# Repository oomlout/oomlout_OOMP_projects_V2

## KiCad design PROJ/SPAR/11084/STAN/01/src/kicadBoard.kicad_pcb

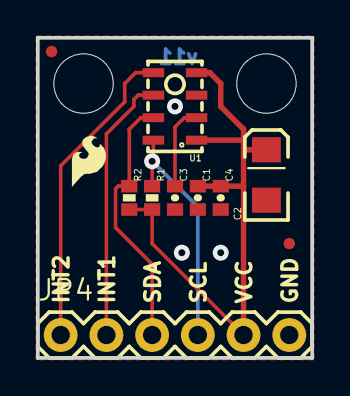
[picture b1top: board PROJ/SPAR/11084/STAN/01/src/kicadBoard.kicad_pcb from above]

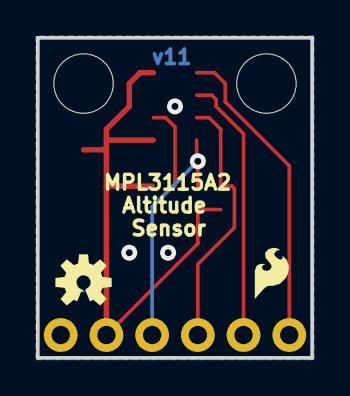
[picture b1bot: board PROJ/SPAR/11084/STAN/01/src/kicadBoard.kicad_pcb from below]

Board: 2 copper layers, 15.2 x 17.8 mm, 16 parts (2 on the bottom side), 7 nets.

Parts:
C1, C3: 0.1uF; 0402-CAP
C2: 10uF; EIA3216
C4: 1uF; 0402-CAP
JP1, JP5: LOGO-SFESK; SFE-LOGO-FLAME
JP2, JP3: STAND-OFF
JP4: 1X06
JP6, JP7: FIDUCIALUFIDUCIAL; MICRO-FIDUCIAL
R1, R2: 1k; 0402-RES
U1: MPL3115A2LGA8; LGA8
U$1: OSHW-LOGOS; OSHW-LOGO-S
U$2: CREATIVE_COMMONS

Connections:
GND: C1.2, C2.C, C3.2, C4.2, JP4.6, U1.3
INT1: JP4.2, U1.6
INT2: JP4.1, U1.5
unnamed: C3.1, U1.2
SCL: JP4.4, R1.1, U1.8
SDA: JP4.3, R2.1, U1.7
VCC: C1.1, C2.A, C4.1, JP4.5, R1.2, R2.2, U1.1, U1.4

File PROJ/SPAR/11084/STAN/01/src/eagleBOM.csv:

"Part";"Value";"Device";"Package";"Description";"";
"C1";"0.1uF";"CAP0402-CAP";"0402-CAP";"Capacitor";"";
"C2";"10uF";"CAP_POL1206";"EIA3216";"Capacitor Polarized";"";
"C3";"0.1uF";"CAP0402-CAP";"0402-CAP";"Capacitor";"";
"C4";"1uF";"CAP0402-CAP";"0402-CAP";"Capacitor";"";
"JP1";"LOGO-SFESK";"LOGO-SFESK";"SFE-LOGO-FLAME";"Spark Fun Electronics PCB Logo";"";
"JP2";"STAND-OFF";"STAND-OFF";"STAND-OFF";"Stand Off";"";
"JP3";"STAND-OFF";"STAND-OFF";"STAND-OFF";"Stand Off";"";
"JP4";"";"M06SIP";"1X06";"Header 6";"";
"JP5";"LOGO-SFESK";"LOGO-SFESK";"SFE-LOGO-FLAME";"Spark Fun Electronics PCB Logo";"";
"JP6";"FIDUCIALUFIDUCIAL";"FIDUCIALUFIDUCIAL";"MICRO-FIDUCIAL";"Fiducial Alignment Points";"";
"JP7";"FIDUCIALUFIDUCIAL";"FIDUCIALUFIDUCIAL";"MICRO-FIDUCIAL";"Fiducial Alignment Points";"";
"R1";"1k";"RESISTOR0402-RES";"0402-RES";"Resistor";"";
"R2";"1k";"RESISTOR0402-RES";"0402-RES";"Resistor";"";
"U$1";"OSHW-LOGOS";"OSHW-LOGOS";"OSHW-LOGO-S";"Open Source Hardware Logo This logo indicates the piece of hardware it is found on incorporates a OSHW license and/or adheres to the definition of open source hardware found here: http://freedomdefined.org/OSHW";"";
"U$2";"CREATIVE_COMMONS";"CREATIVE_COMMONS";"CREATIVE_COMMONS";"";"";
"U1";"MPL3115A2LGA8";"MPL3115A2LGA8";"LGA8";"Altimeter/Pressure Sensor, I2C, 1.95V-3.6V supply, 50 to 110kPa";"";

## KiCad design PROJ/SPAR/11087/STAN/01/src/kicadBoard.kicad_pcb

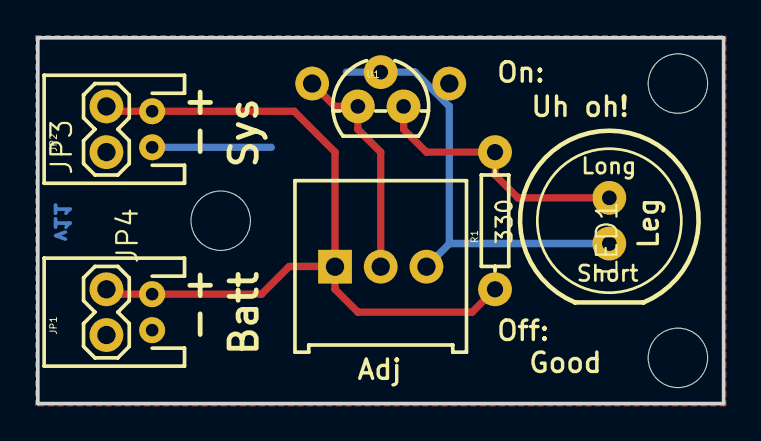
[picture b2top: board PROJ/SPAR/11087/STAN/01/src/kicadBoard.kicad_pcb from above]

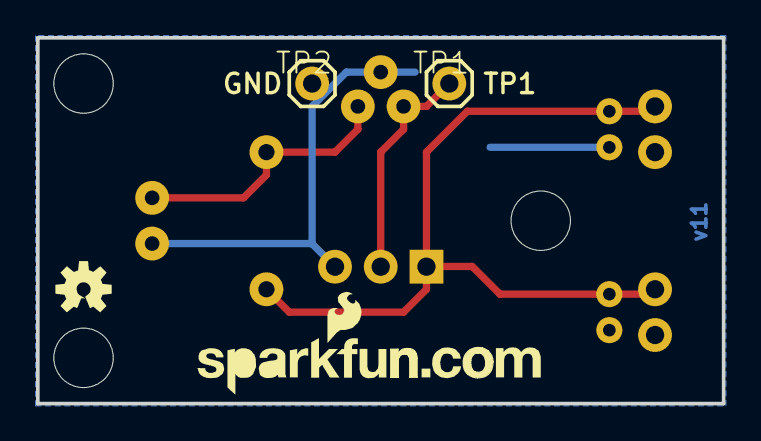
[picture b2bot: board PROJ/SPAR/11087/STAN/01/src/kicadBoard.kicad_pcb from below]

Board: 2 copper layers, 38.1 x 20.3 mm, 16 parts (4 on the bottom side), 4 nets.

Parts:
JP1: Battery; JST-2-PTH
JP2: System; JST-2-PTH
JP3, JP4: 1X02
JP31, JP41, JP61: STAND-OFF
JP51: LOGO-SFENEW; SFE-NEW-WEBLOGO
LED1: Green; LED10MM-2
R1: 330; AXIAL-0.3
RADJ0: 10K; 3386U
TP1: TP1; 1X01
TP2: TP2; 1X01
U1: TL431; TO-92
U$1: OSHW-LOGOS; OSHW-LOGO-S
U$2: CREATIVE_COMMONS

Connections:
GND: JP1.1, JP2.1, JP3.1, JP4.2, LED1.K, RADJ0.3, TP2.1, U1.2
VCC: JP1.2, JP2.2, JP3.2, JP4.1, R1.P$1, RADJ0.1
VCUTOFF: RADJ0.2, TP1.1, U1.1
VOUT: LED1.A, R1.P$2, U1.3

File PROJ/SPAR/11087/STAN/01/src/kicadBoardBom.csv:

"Id";"Designator";"Package";"Quantity";"Designation";"Supplier and ref";
1;"U$2";"CREATIVE_COMMONS";1;"CREATIVE_COMMONS";;;
2;"JP31,JP41,JP61";"STAND-OFF";3;"STAND-OFF";;;
3;"U1";"TO-92";1;"TL431";;;
4;"RADJ0";"3386U";1;"10K";;;
5;"JP1";"JST-2-PTH";1;"Battery";;;
6;"JP3,JP4";"1X02";2;"";;;
7;"LED1";"LED10MM-2";1;"Green";;;
8;"JP2";"JST-2-PTH";1;"System";;;
9;"R1";"AXIAL-0.3";1;"330";;;
10;"TP1";"1X01";1;"TP1";;;
11;"JP51";"SFE-NEW-WEBLOGO";1;"LOGO-SFENEW";;;
12;"U$1";"OSHW-LOGO-S";1;"OSHW-LOGOS";;;
13;"TP2";"1X01";1;"TP2";;;

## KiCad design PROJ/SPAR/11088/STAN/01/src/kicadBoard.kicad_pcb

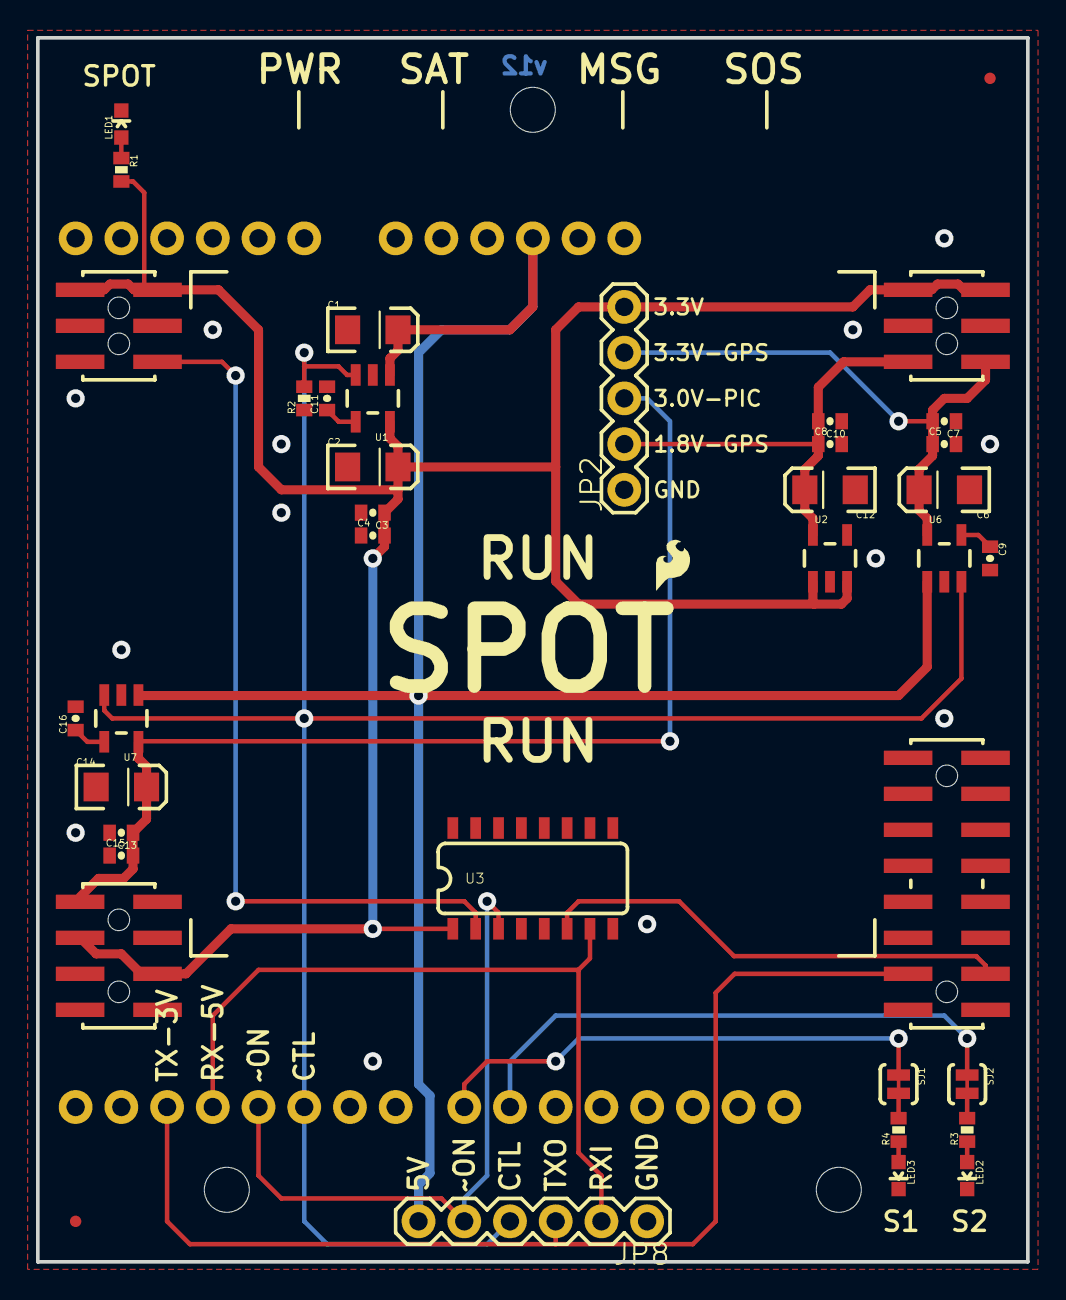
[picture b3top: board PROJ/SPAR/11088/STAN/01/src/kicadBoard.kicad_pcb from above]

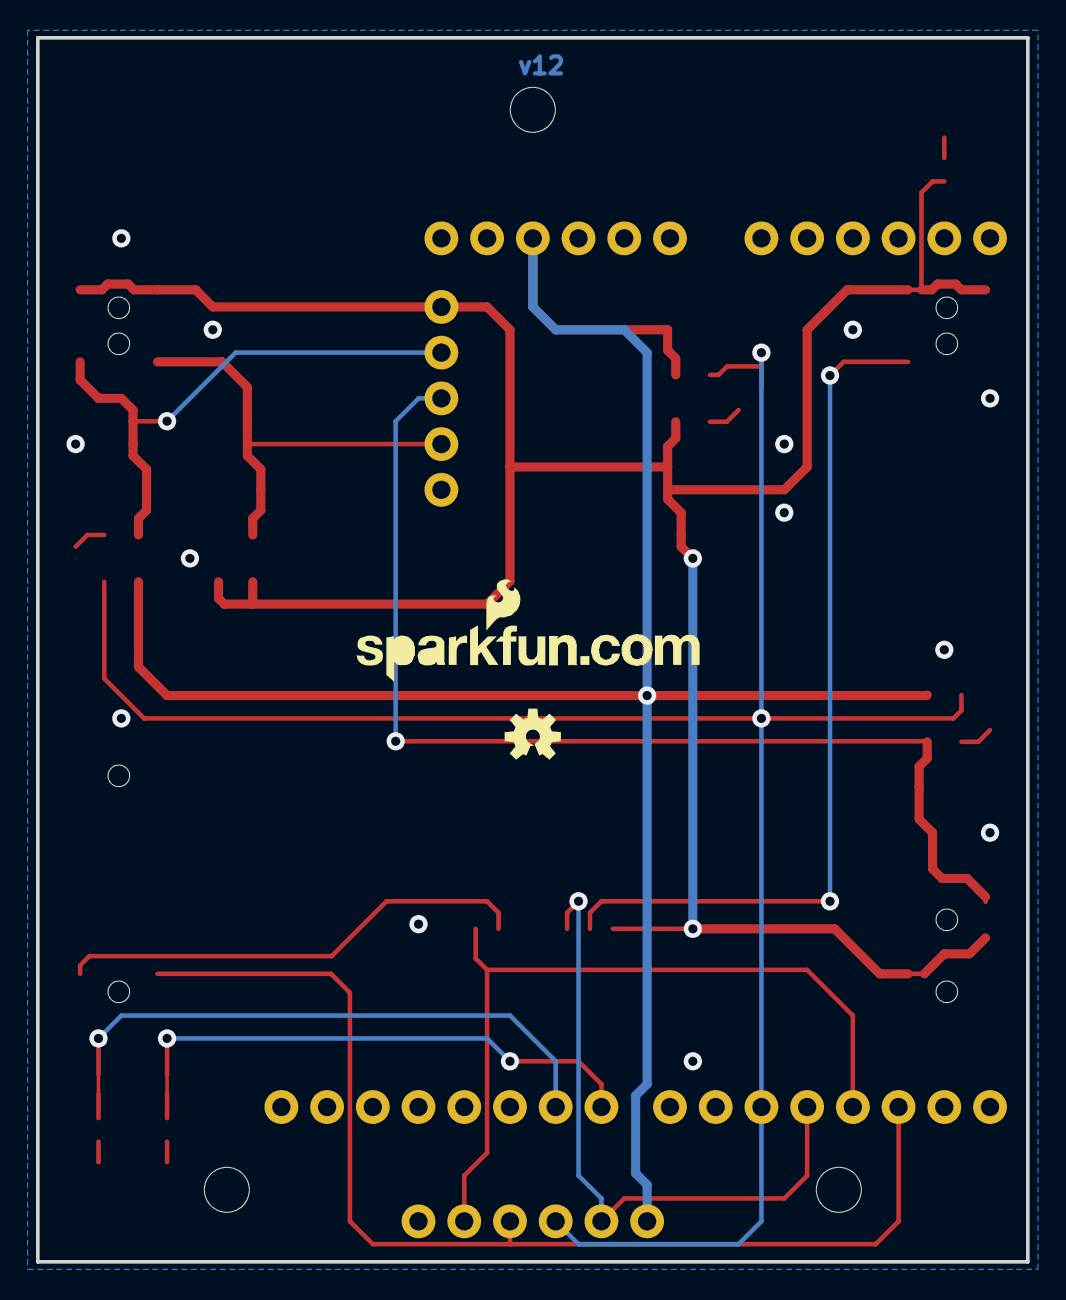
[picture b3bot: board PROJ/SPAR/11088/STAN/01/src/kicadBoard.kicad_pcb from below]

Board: 2 copper layers, 55.0 x 68.0 mm, 40 parts (2 on the bottom side), 22 nets.

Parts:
C1, C2, C6, C12, C14: 10uF; EIA3216
C3, C5, C8, C13: 1uF; 0402-CAP
C4, C7, C10, C15: 0.1uF; 0402-CAP
C9, C11, C16: 470nF; 0402-CAP
JP2: 1X05
JP8: 1X06
JP10, JP11: FIDUCIALUFIDUCIAL; MICRO-FIDUCIAL
LED1: Red; LED-0603
LED2: Blue; LED-0603
LED3: Green; LED-0603
R1, R3, R4: 330; 0402-RES
R2: 10K; 0402-RES
SJ1, SJ2: SJ_2S-TRACE
U1: MIC5219-3.3; SOT23-5
U2: AP7311-1.8; SOT23-5
U3: 74HC4050; SO016
U4: SPOT-CONNECT
U5: ARDUINO_SHIELD; DUEMILANOVE_VIAS
U6, U7: MIC5219-3.0; SOT23-5
U$1: LOGO-SFESK; SFE-LOGO-FLAME
U$2: CREATIVE_COMMONS
U$3: OSHW-LOGOS; OSHW-LOGO-S
U$11: LOGO-SFENEW; SFE-NEW-WEBLOGO

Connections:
1.8V-GPS: C8.1, C10.2, C12.A, JP2.2, U2.5, U4.1.8V-GPS
3.3V: C2.A, C3.1, C4.2, JP2.5, R1.2, U1.5, U2.1, U2.3, U3.1, U4.3.3V@1, U4.3.3V@2, U4.3.3V@3, U4.3.3V@4, U4.3VMSP, U4.BATT
3V-GPS: C5.1, C6.A, C7.2, JP2.4, U4.3V-GPS, U6.5
3V-PIC: C13.1, C14.A, C15.2, JP2.3, U4.3VPIC, U7.5
5V: C1.A, JP8.6, U1.1, U5.5V, U6.1, U7.1
GND: C1.C, C2.C, C3.2, C4.1, C5.2, C6.C, C7.1, C8.2, C9.2, C10.1, C11.2, C12.C, C13.2, C14.C, C15.1, C16.2, JP2.1, JP8.1, LED1.C, LED2.C, LED3.C, R2.1, U1.2, U2.2, U3.8, U4.GND@1, U4.GND@2, U4.GND@3, U4.GND@4, U4.GND@5, U5.GND@0, U5.GND@1, U5.GND@2, U6.2, U7.2
unnamed: C16.1, U7.4
unnamed: R4.2, SJ1.2
unnamed: R3.2, SJ2.2
unnamed: C9.1, U6.4
unnamed: LED2.A, R3.1
unnamed: LED3.A, R4.1
unnamed: SJ1.1, U5.D8
unnamed: SJ2.1, U5.D9
unnamed: C11.1, U1.4
unnamed: LED1.A, R1.1
PWRCTL: JP8.4, R2.2, U1.3, U5.D5, U6.3, U7.3
SPOT-RX-3V: U3.6, U4.BT-TX
SPOT-RX-5V: JP8.2, U3.7, U5.D3
SPOT-TX-3V: JP8.3, U4.BT-RX, U5.D2
~ON-3V: U3.2, U4.ON/OFF
~ON-5V: JP8.5, U3.3, U5.D4

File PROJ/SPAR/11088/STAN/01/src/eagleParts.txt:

Partlist

Exported from boardEagle.brd at 17/08/2022 19:31

EAGLE Version 9.6.2 Copyright (c) 1988-2020 Autodesk, Inc.

Assembly variant: 

Part     Value             Package          Library  Position (inch)       Orientation

C1       10uF              EIA3216          SparkFun (0.73 2.04)           R0
C2       10uF              EIA3216          SparkFun (0.73 1.74)           R0
C3       1uF               0402-CAP         SparkFun (0.73 1.64)           R180
C4       0.1uF             0402-CAP         SparkFun (0.73 1.59)           R0
C5       1uF               0402-CAP         SparkFun (1.98 1.79)           R0
C6       10uF              EIA3216          SparkFun (1.98 1.69)           R180
C7       0.1uF             0402-CAP         SparkFun (1.98 1.84)           R180
C8       1uF               0402-CAP         SparkFun (1.73 1.79)           R0
C9       470nF             0402-CAP         SparkFun (2.08 1.54)           R270
C10      0.1uF             0402-CAP         SparkFun (1.73 1.84)           R180
C11      470nF             0402-CAP         SparkFun (0.63 1.89)           R90
C12      10uF              EIA3216          SparkFun (1.73 1.69)           R180
C13      1uF               0402-CAP         SparkFun (0.18 0.94)           R180
C14      10uF              EIA3216          SparkFun (0.18 1.04)           R0
C15      0.1uF             0402-CAP         SparkFun (0.18 0.89)           R0
C16      470nF             0402-CAP         SparkFun (0.08 1.19)           R90
JP2                        1X05             SparkFun (1.28 1.69)           R90
JP8                        1X06             SparkFun (1.33 0.09)           R180
JP10     FIDUCIALUFIDUCIAL MICRO-FIDUCIAL   SparkFun (2.08 2.59)           R90
JP11     FIDUCIALUFIDUCIAL MICRO-FIDUCIAL   SparkFun (0.08 0.09)           R90
LED1     Red               LED-0603         SparkFun (0.18 2.49)           R0
LED2     Blue              LED-0603         SparkFun (2.03 0.19)           R180
LED3     Green             LED-0603         SparkFun (1.88 0.19)           R180
R1       330               0402-RES         SparkFun (0.18 2.39)           R270
R2       10K               0402-RES         SparkFun (0.58 1.89)           R90
R3       330               0402-RES         SparkFun (2.03 0.29)           R90
R4       330               0402-RES         SparkFun (1.88 0.29)           R90
SJ1                        SJ_2S-TRACE      SparkFun (1.88 0.39)           R270
SJ2                        SJ_2S-TRACE      SparkFun (2.03 0.39)           R270
U1       MIC5219-3.3       SOT23-5          SparkFun (0.73 1.89)           R180
U2       AP7311-1.8        SOT23-5          SparkFun (1.73 1.54)           R0
U3       74HC4050          SO016            SparkFun (1.08 0.84)           R0
U4       SPOT-CONNECT      SPOT-CONNECT     SparkFun (1.08 1.34)           R0
U5       ARDUINO_SHIELD    DUEMILANOVE_VIAS SparkFun (1.73 0.24)           R90
U6       MIC5219-3.0       SOT23-5          SparkFun (1.98 1.54)           R0
U7       MIC5219-3.0       SOT23-5          SparkFun (0.18 1.19)           R180

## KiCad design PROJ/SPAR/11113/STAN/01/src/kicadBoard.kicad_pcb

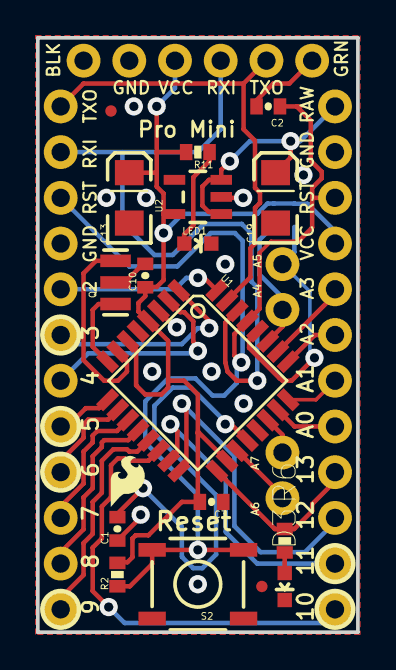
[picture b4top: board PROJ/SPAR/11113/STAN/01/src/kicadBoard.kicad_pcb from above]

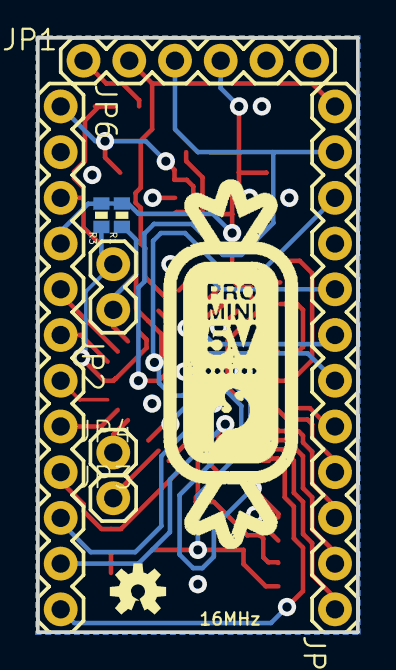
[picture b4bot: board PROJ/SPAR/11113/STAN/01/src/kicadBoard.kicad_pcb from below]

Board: 2 copper layers, 17.8 x 33.0 mm, 29 parts (10 on the bottom side), 32 nets.

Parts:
C1, C2, C3, C10: 0.1uF; 0402-CAP
C13, C19: 10uF; EIA3216
D3: Green; LED-0603
FRAME1: FRAME-LETTER; CREATIVE_COMMONS
JP1: FTDI Basic; 1X06
JP2: 1X02
JP3, JP4: 1X01
JP5, JP8: FIDUCIALUFIDUCIAL; MICRO-FIDUCIAL
JP6, JP7: 1X12
LED1: Red; LED-0603
Q1: 8/16/20MHz; RESONATOR-SMD
R1, R3: 0402-RES
R2, R11: 10K; 0402-RES
R6: 330; 0402-RES
S2: Reset; TACTILE_SWITCH_SMD
U1: ATMEGA328; TQFP32-08
U2: MIC5205; SOT23-5
U$1: LOGO-SFESK; SFE-LOGO-FLAME
U$2: PRO_MINI_CANDY
U$3: OSHW-LOGOS; OSHW-LOGO-S

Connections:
A0: JP6.8, U1.23
A1: JP6.7, U1.24
A2: JP6.6, U1.25
A3: JP6.5, U1.26
A4: JP2.1, R1.1, U1.27
A5: JP2.2, R3.1, U1.28
A6: JP3.1, U1.19
A7: JP4.1, U1.22
AREF: C1.2, U1.20
D2: JP7.8, U1.32
D3: JP7.7, U1.1
D4: JP7.6, U1.2
D5: JP7.5, U1.9
D6: JP7.4, U1.10
D7: JP7.3, U1.11
D8: JP7.2, U1.12
D9: JP7.1, U1.13
D10: JP6.12, U1.14
DTR: C2.2, JP1.1
GND: C1.1, C3.1, C10.2, C13.C, C19.C, D3.C, JP1.5, JP1.6, JP6.2, JP7.9, LED1.C, Q1.2, S2.1, S2.2, U1.3, U1.5, U1.21, U2.2
MISO: JP6.10, U1.16
MOSI: JP6.11, U1.15
unnamed: Q1.1, U1.8
unnamed: Q1.3, U1.7
unnamed: D3.A, R6.2
unnamed: LED1.A, R11.1
RAW: C19.A, JP6.1, U2.1, U2.3
RESET: C2.1, JP6.3, JP7.10, R2.1, S2.3, S2.4, U1.29
RXI: JP1.3, JP7.11, U1.30
SCK: JP6.9, R6.1, U1.17
TXO: JP1.2, JP7.12, U1.31
VCC: C3.2, C10.1, C13.A, JP1.4, JP6.4, R1.2, R2.2, R3.2, R11.2, U1.4, U1.6, U1.18, U2.5

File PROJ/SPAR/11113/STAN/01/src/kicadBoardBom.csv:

"Id";"Designator";"Package";"Quantity";"Designation";"Supplier and ref";
1;"C19,C13";"EIA3216";2;"10uF";;;
2;"C2,C1,C10,C3";"0402-CAP";4;"0.1uF";;;
3;"R11,R2";"0402-RES";2;"10K";;;
4;"R6";"0402-RES";1;"330";;;
5;"JP5,JP8";"MICRO-FIDUCIAL";2;"FIDUCIALUFIDUCIAL";;;
6;"D3";"LED-0603";1;"Green";;;
7;"Q1";"RESONATOR-SMD";1;"8/16/20MHz";;;
8;"FRAME1";"CREATIVE_COMMONS";1;"FRAME-LETTER";;;
9;"U1";"TQFP32-08";1;"ATMEGA328";;;
10;"U2";"SOT23-5";1;"MIC5205";;;
11;"U$1";"SFE-LOGO-FLAME";1;"LOGO-SFESK";;;
12;"LED1";"LED-0603";1;"Red";;;
13;"S2";"TACTILE_SWITCH_SMD";1;"Reset";;;
14;"JP1";"1X06";1;"FTDI Basic";;;
15;"U$3";"OSHW-LOGO-S";1;"OSHW-LOGOS";;;
16;"U$2";"PRO_MINI_CANDY";1;"PRO_MINI_CANDY";;;
17;"R3,R1";"0402-RES";2;"";;;
18;"JP7,JP6";"1X12";2;"";;;
19;"JP2";"1X02";1;"";;;
20;"JP3,JP4";"1X01";2;"";;;

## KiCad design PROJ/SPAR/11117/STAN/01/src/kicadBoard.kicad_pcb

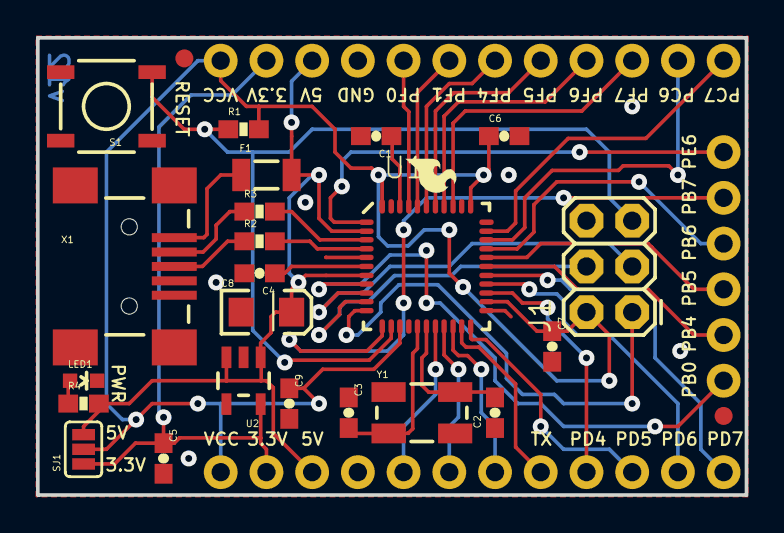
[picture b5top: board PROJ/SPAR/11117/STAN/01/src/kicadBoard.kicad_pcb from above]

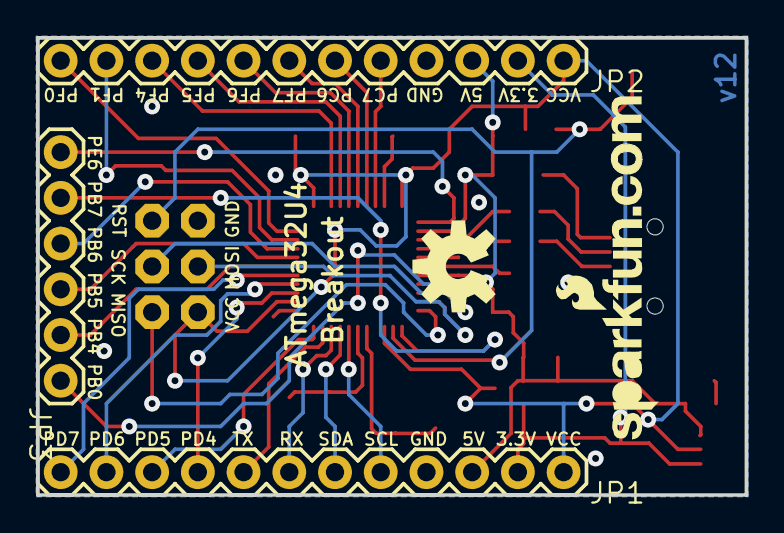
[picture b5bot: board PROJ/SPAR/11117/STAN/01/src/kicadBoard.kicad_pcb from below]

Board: 2 copper layers, 39.4 x 25.4 mm, 30 parts (5 on the bottom side), 40 nets.

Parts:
C1, C6, C7, C9: 0.1uF; 0603-CAP
C2, C3: 18pF; 0603-CAP
C4, C5: 1uF; 0603-CAP
C8: 10uF; EIA3216
F1: PTCSMD; PTC-1206
J1: AVR_SPI_PRG; 2X3
JP1, JP2: M12PTH; 1X12
JP3: 1X06
JP5: LOGO-SFESK; SFE-LOGO-FLAME
JP6, JP7: FIDUCIAL1X2; FIDUCIAL-1X2
JP8: LOGO-SFENEW; SFE-NEW-WEBLOGO
LED1: Power; LED-0603
R1: 10k; 0603-RES
R2, R3: 22; 0603-RES
R4: 1k; 0603-RES
S1: SWITCH-SMD; TACTILE_SWITCH_SMD
SJ1: Power Select; SJ_3_PASTE2&3
U1: ATMEGA32U4; QFN-44-NOPAD_1_1
U2: 3.3V_REG_LDOSMD; SOT23-5
U$6: OSHW-LOGOM; OSHW-LOGO-M
X1: USBSMD; USB-MINIB
Y1: 16MHz; CRYSTAL-SMD-5X3

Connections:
3.3V: C5.1, JP1.2, JP2.2, SJ1.1, U2.5
5V: C8.A, F1.2, JP1.3, JP2.3, R4.2, SJ1.3, U1.2, U1.7, U2.1, U2.3
AREF: C1.1, U1.42
D+: R2.1, X1.D+
D-: R3.1, X1.D-
GND: C1.2, C2.1, C3.1, C4.2, C5.2, C6.2, C7.2, C8.C, C9.2, J1.6, JP1.4, JP2.4, LED1.C, S1.1, U1.5, U1.15, U1.23, U1.33, U1.35, U1.43, U2.2, X1.GND
MISO: J1.1, U1.11
MOSI: J1.4, U1.10
unnamed: C2.2, U1.17, Y1.3
unnamed: C3.2, U1.16, Y1.1
unnamed: F1.1, X1.VBUS
unnamed: R2.2, U1.4
unnamed: R3.2, U1.3
unnamed: LED1.A, R4.1
PB0: JP3.1, U1.8
PB4: JP3.2, U1.28
PB5: JP3.3, U1.29
PB6: JP3.4, U1.30
PB7: JP3.5, U1.12
PC6: JP2.11, U1.31
PC7: JP2.12, U1.32
PD4: JP1.9, U1.25
PD5: JP1.10, U1.22
PD6: JP1.11, U1.26
PD7: JP1.12, U1.27
PE6: JP3.6, U1.1
PF0: JP2.5, U1.41
PF1: JP2.6, U1.40
PF4: JP2.7, U1.39
PF5: JP2.8, U1.38
PF6: JP2.9, U1.37
PF7: JP2.10, U1.36
RST: J1.5, R1.1, S1.3, U1.13
RX: JP1.7, U1.20
SCK: J1.3, U1.9
SCL: JP1.5, U1.18
SDA: JP1.6, U1.19
TX: JP1.8, U1.21
UCAP: C4.1, U1.6
VCC: C6.1, C7.1, C9.1, J1.2, JP1.1, JP2.1, R1.2, SJ1.2, U1.14, U1.24, U1.34, U1.44

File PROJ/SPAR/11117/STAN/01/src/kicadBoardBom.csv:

"Id";"Designator";"Package";"Quantity";"Designation";"Supplier and ref";
1;"U2";"SOT23-5";1;"3.3V_REG_LDOSMD";;;
2;"U1";"QFN-44-NOPAD_1_1";1;"ATMEGA32U4";;;
3;"JP5";"SFE-LOGO-FLAME";1;"LOGO-SFESK";;;
4;"Y1";"CRYSTAL-SMD-5X3";1;"16MHz";;;
5;"C2,C3";"0603-CAP";2;"18pF";;;
6;"R3,R2";"0603-RES";2;"22";;;
7;"C9,C6,C1,C7";"0603-CAP";4;"0.1uF";;;
8;"F1";"PTC-1206";1;"PTCSMD";;;
9;"JP7,JP6";"FIDUCIAL-1X2";2;"FIDUCIAL1X2";;;
10;"SJ1";"SJ_3_PASTE2&3";1;"Power Select";;;
11;"C5,C4";"0603-CAP";2;"1uF";;;
12;"X1";"USB-MINIB";1;"USBSMD";;;
13;"R4";"0603-RES";1;"1k";;;
14;"R1";"0603-RES";1;"10k";;;
15;"LED1";"LED-0603";1;"Power";;;
16;"C8";"EIA3216";1;"10uF";;;
17;"J1";"2X3";1;"AVR_SPI_PRG";;;
18;"S1";"TACTILE_SWITCH_SMD";1;"SWITCH-SMD";;;
19;"JP2,JP1";"1X12";2;"M12PTH";;;
20;"JP3";"1X06";1;"";;;
21;"JP8";"SFE-NEW-WEBLOGO";1;"LOGO-SFENEW";;;
22;"U$6";"OSHW-LOGO-M";1;"OSHW-LOGOM";;;

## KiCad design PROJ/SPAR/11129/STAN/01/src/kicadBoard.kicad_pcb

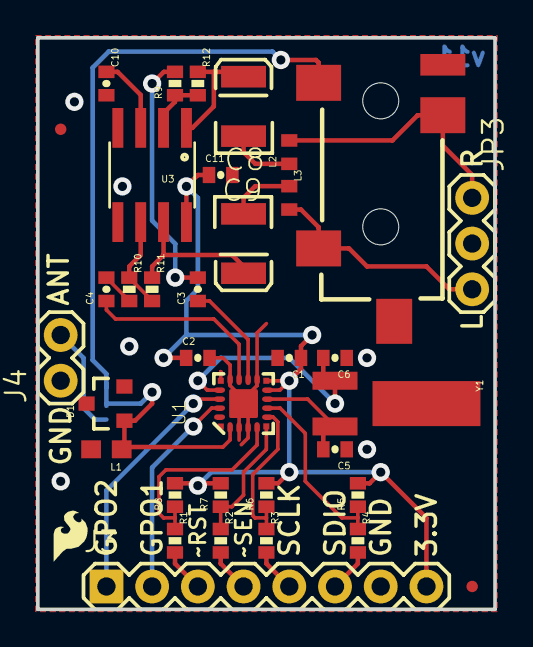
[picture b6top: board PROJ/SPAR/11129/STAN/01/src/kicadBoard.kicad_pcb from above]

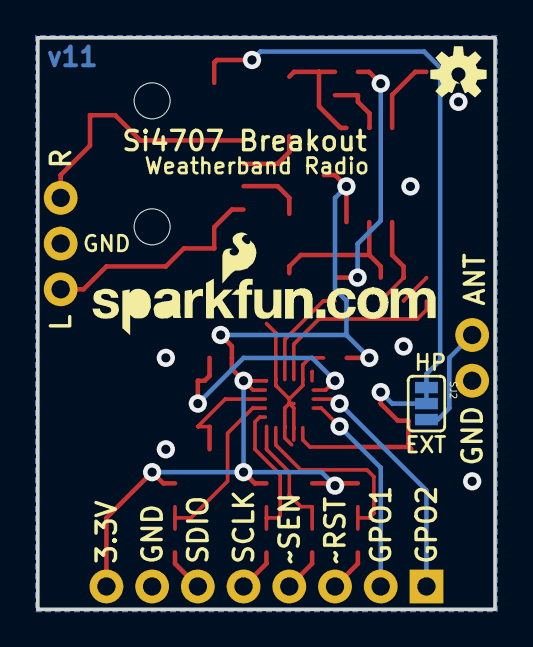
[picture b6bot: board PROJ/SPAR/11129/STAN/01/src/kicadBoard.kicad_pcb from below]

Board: 2 copper layers, 25.4 x 31.8 mm, 40 parts (3 on the bottom side), 30 nets.

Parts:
C1: 22nF; 0402-CAP
C2, C10, C11: 0.1uF; 0402-CAP
C3, C4: 0.39uF; 0402-CAP
C5, C6: 22pF; 0402-CAP
C8, C9: 47uF; EIA3528
D1: CM1213; SOT23-3
FRAME1: FRAME-LETTER; CREATIVE_COMMONS
J3: OUTPUT; 1X08
J4: ANT; 1X02
JP1: LOGO-SFENEW; SFE-NEW-WEBLOGO
JP2: LOGO-SFESK; SFE-LOGO-FLAME
JP3: 1X03
JP4, JP5: FIDUCIALUFIDUCIAL; MICRO-FIDUCIAL
L1: 56nH; 0603
L2, L3: Ferrite 2.5k; C0402
R1, R2, R3, R4: 2k; 0402-RES
R5, R6: 4.7k; 0402-RES
R7, R8: 10k; 0402-RES
R9, R10: 20k; 0402-RES
R11, R12: 47k; 0402-RES
SJ2: SJ_3
U1: SI470X
U2: AUDIO-JACK-3.5MM-SMD
U3: TPA6111; SPARKFUN_SO08
U$2: OSHW-LOGOS; OSHW-LOGO-S
Y1: 32.768kHz; CRYSTAL-32KHZ-SMD

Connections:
3.3V: C1.1, C2.1, C11.1, J3.8, R5.2, R6.2, R7.2, R8.2, U1.10, U1.11, U3.8
GND: C1.2, C2.2, C5.1, C6.1, C10.2, C11.2, D1.2, D1.3, J3.7, J4.1, JP3.2, L1.2, U1.3, U1.4, U1.12, U1.15, U1.16, U1.21, U3.4, U3.5
GPO1: J3.2, U1.19
GPO2: J3.1, U1.18
J1: D1.1, L1.1, SJ2.2, U1.2
LA: JP3.3, L3.2, U2.TIP
LOUT: C4.1, U1.14
unnamed: C3.2, R9.2
unnamed: C4.2, R10.2
unnamed: C6.2, U1.17, Y1.X1
unnamed: SJ2.1, U2.SLEEVE
unnamed: J4.2, SJ2.3
unnamed: R9.1, R12.2, U3.2
unnamed: R10.1, R11.2, U3.6
unnamed: C10.1, U3.3
unnamed: C8.C, L2.1
unnamed: C9.C, L3.1
unnamed: C8.A, R12.1, U3.1
unnamed: C9.A, R11.1, U3.7
RA: JP3.1, L2.2, U2.RING
RCLK: C5.2, U1.9, Y1.X2
ROUT: C3.1, U1.13
RST-O: J3.3, R1.2
SCLK: R3.1, R6.1, U1.7
SCLK-O: J3.5, R3.2
SDIO: R4.1, R5.1, U1.8
SDIO-O: J3.6, R4.2
SEN-O: J3.4, R2.2
~RST: R1.1, R8.1, U1.5
~SEN: R2.1, R7.1, U1.6

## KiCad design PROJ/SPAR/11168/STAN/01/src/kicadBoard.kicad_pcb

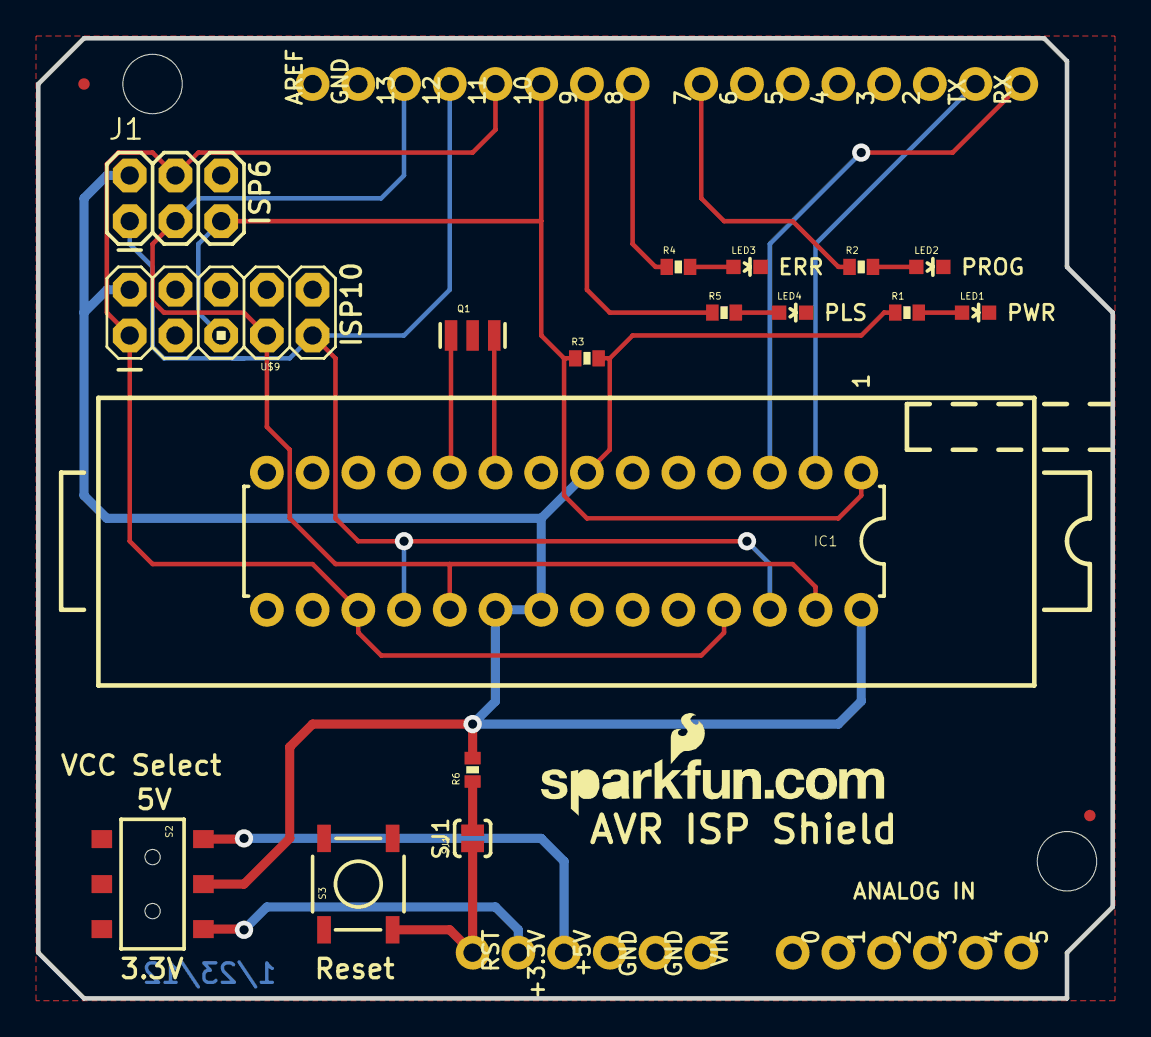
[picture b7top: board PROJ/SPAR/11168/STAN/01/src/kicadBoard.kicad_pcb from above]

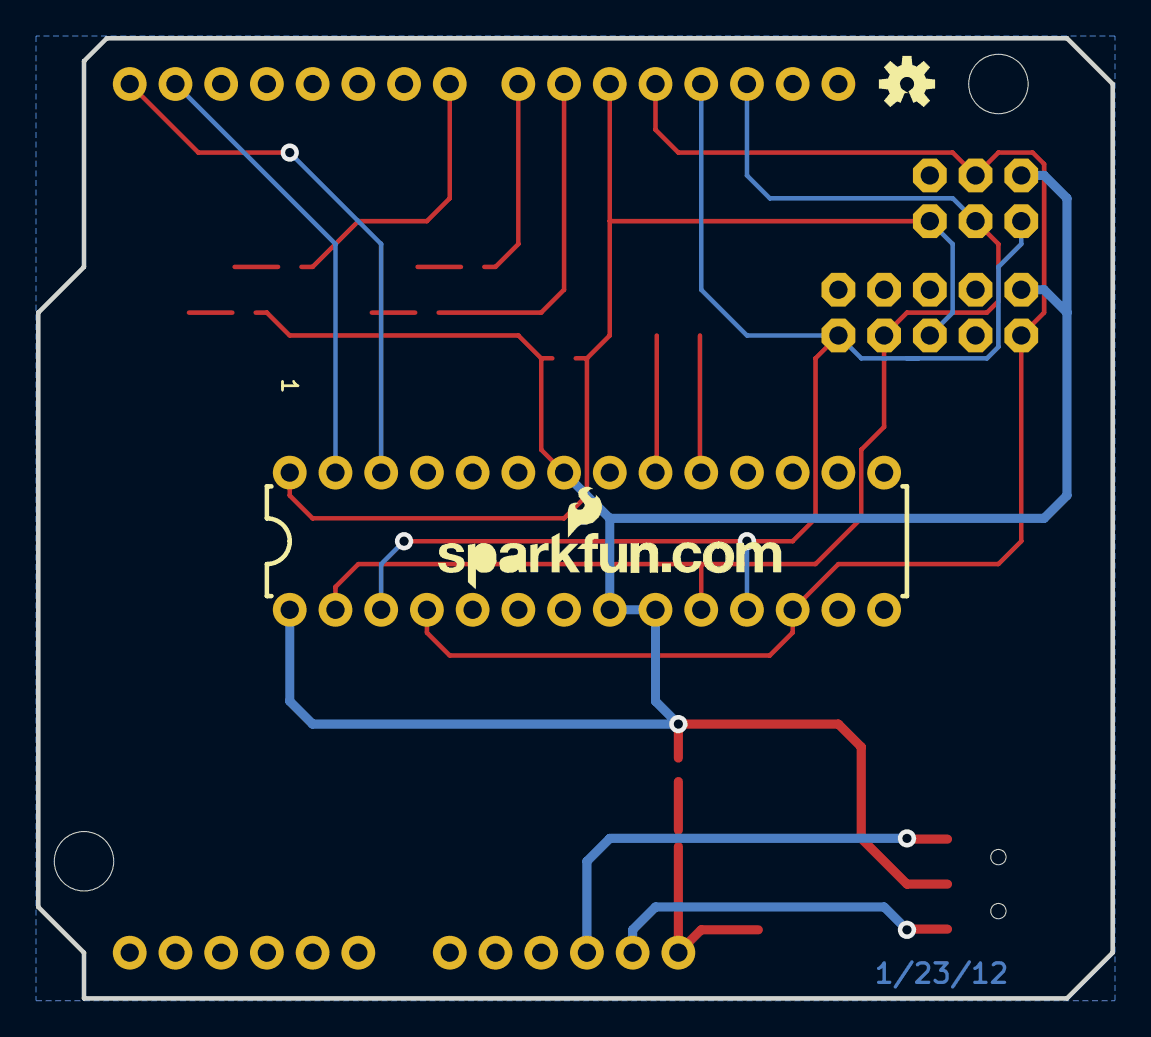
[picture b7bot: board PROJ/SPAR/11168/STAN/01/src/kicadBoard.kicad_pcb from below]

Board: 2 copper layers, 59.7 x 53.3 mm, 24 parts (2 on the bottom side), 21 nets.

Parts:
$$U$1: CREATIVE_COMMONS
IC1: AVR-MEGA-PZIF_SOCKET; DIL28-3-ZIF_SOCKET
J1: AVR_SPI_PRG_6PTH; 2X3
JP5, JP6: FIDUCIAL1X2.5; FIDUCIAL-1X2.5
LED1, LED2: GREEN; LED-0603
LED3: RED; LED-0603
LED4: BLUE; LED-0603
Q1: 8/16/20MHz; RESONATOR-SMD
R1, R2, R4, R5: 330; 0402-RES
R3: 10K; 0402-RES
R6: 100; 0402-RES
S2: AYZ0202
S3: Reset; TACTILE_SWITCH_SMD
SJ1: SOLDERJUMPERNO; SJ_2S-NO
U1: ARDUINO_SHIELDLABEL; DUEMILANOVE_SHIELD
U$4: OSHW-LOGOS; OSHW-LOGO-S
U$7, U$12: SFE-NEW-WEBLOGO
U$9: AVR_SPI_PROG; AVR_ICSP

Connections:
3.3V: S2.3, U1.3.3V
5V: S2.1, U1.5V
D7: R2.1, U1.D7
D8: R4.1, U1.D8
D9: R5.1, U1.D9
GND: IC1.4, IC1.8, IC1.22, J1.6, LED1.C, LED2.C, LED3.C, LED4.C, Q1.2, S3.1, U1.GND@0, U1.GND@1, U1.GND@2, U$9.4, U$9.6, U$9.8, U$9.10
MISO: IC1.18, IC1.26, J1.1, U1.D12, U$9.9
MOSI: IC1.17, IC1.25, J1.4, U1.D11, U$9.1
unnamed: LED1.A, R1.2
unnamed: LED2.A, R2.2
unnamed: LED3.A, R4.2
unnamed: LED4.A, R5.2
unnamed: R6.1, SJ1.2
RES: S3.3, SJ1.1, U1.RES
RX: IC1.3, U1.RX
SCK: IC1.19, IC1.27, J1.3, U1.D13, U$9.7
SLV_RST: IC1.1, J1.5, R3.1, U1.D10, U$9.5
TX: IC1.2, U1.TX
VCC: IC1.7, IC1.20, IC1.21, IC1.28, J1.2, R1.1, R3.2, R6.2, S2.2, U$9.2
XTAL1: IC1.9, Q1.3
XTAL2: IC1.10, Q1.1

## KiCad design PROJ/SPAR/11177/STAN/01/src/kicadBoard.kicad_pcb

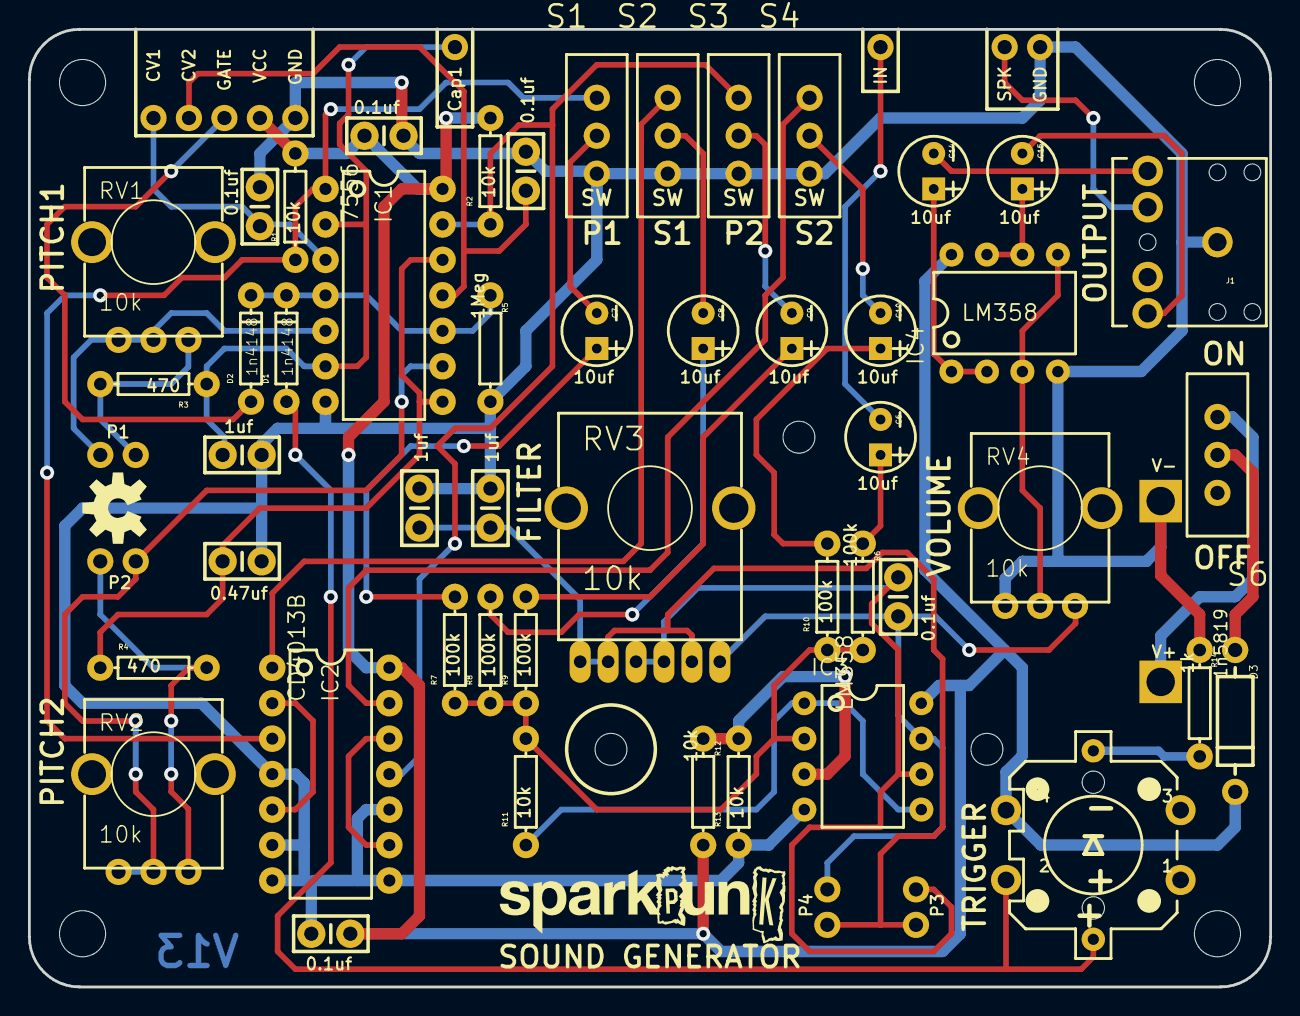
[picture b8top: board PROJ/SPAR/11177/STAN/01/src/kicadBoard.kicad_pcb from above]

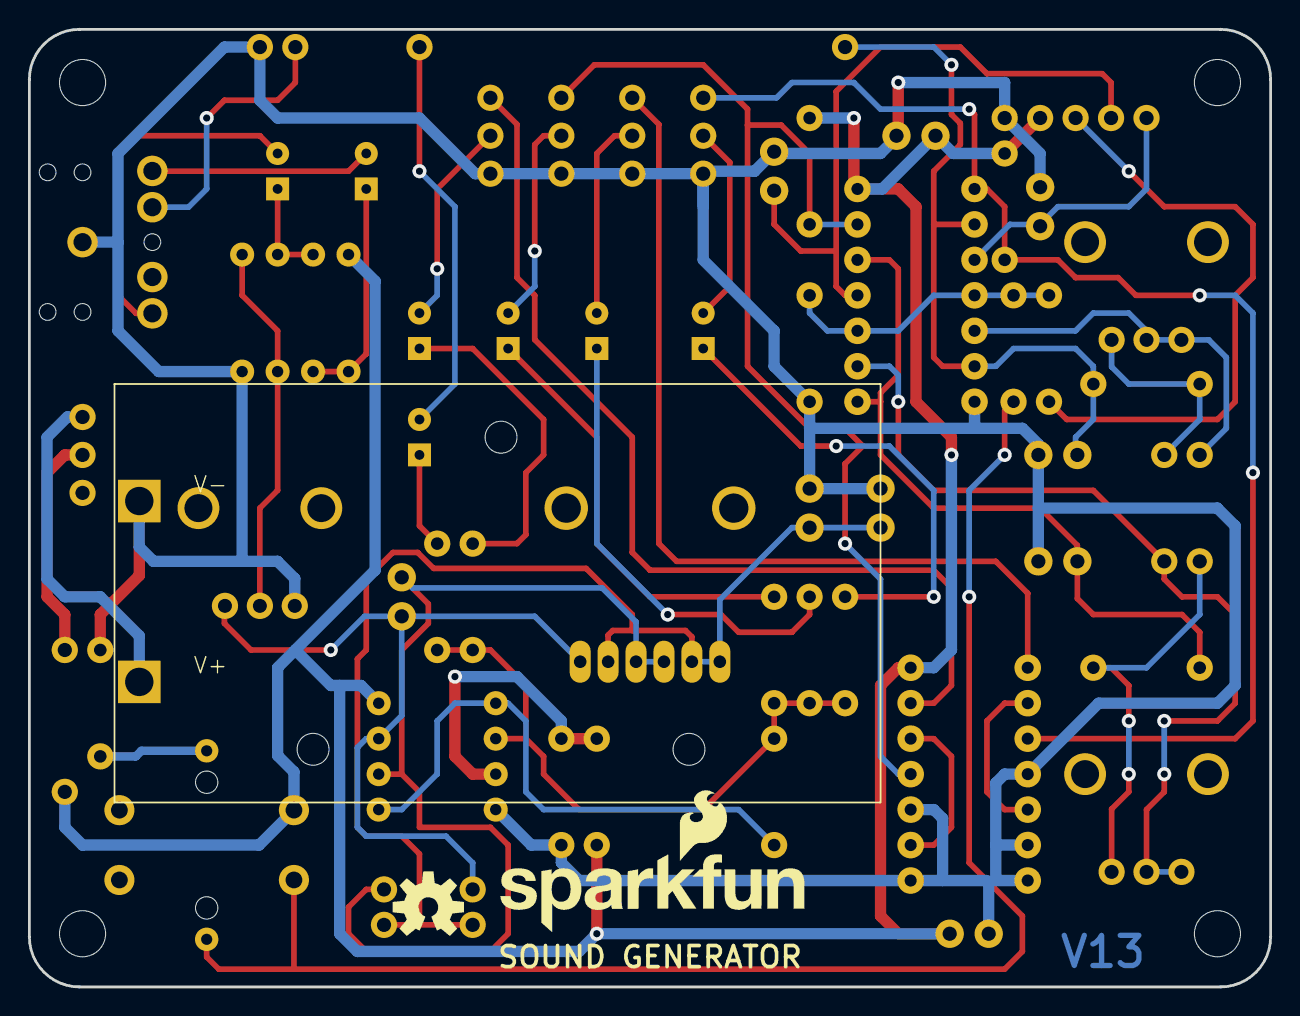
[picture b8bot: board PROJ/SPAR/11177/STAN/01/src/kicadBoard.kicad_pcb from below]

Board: 2 copper layers, 88.9 x 68.6 mm, 75 parts (3 on the bottom side), 44 nets.

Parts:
BAT1: 9V; BC9VPC_KIT
C1, C2, C5, C11, C16: .1uf; CAP-PTH-SMALL-KIT
C3, C12, C13: 1uf; CAP-PTH-SMALL-KIT
C4: .47uf; CAP-PTH-SMALL-KIT
C6, C7, C8, C9, C10, C14, C15: 10uf/25V; CPOL-RADIAL-10UF-25V-KIT
D1, D2: 1n4148; DIODE-1N4148-KIT
D3: 1n5819; DIODE-1N4001-KIT
FRAME1: FRAME-LEDGER; CREATIVE_COMMONS
IC1: 7556; DIL14-KIT
IC2: CD4013B; DIL14-KIT
IC3, IC4: LM358; DIP08-KIT
J1: AUDIO-JACK2KIT; AUDIO-JACK-KIT
JP1: CV1; 1X01NS
JP2: CV2; 1X01NS
JP3, JP4: P1; 1X01NS
JP5, JP6: P2; 1X01NS
JP7: CAP1; 1X01NS
JP8: GATE; 1X01NS
JP9: IN; 1X01NS
JP10, JP11: P3; 1X01NS
JP12, JP13: P4; 1X01NS
JP14: SPK; 1X01NS
JP15, JP17: GND; 1X01NS
JP16: VCC; 1X01NS
LOGO1: SFE_LOGO_NAME_FLAME.2_INCH; SFE_LOGO_NAME_FLAME_.2
LOGO2: SPARKPUNK_LOGO.1INCH_TALL; SPARKPUNK_LOGO_.1
LOGO3, LOGO4: OSHW-LOGOM; OSHW-LOGO-M
R1, R2, R11, R12, R13: 10k; AXIAL-0.3EZ
R3, R4: 470; AXIAL-0.3EZ
R5: 1Meg; AXIAL-0.3EZ
R6, R7, R8, R9, R10: 100k; AXIAL-0.3EZ
R14: 1k; AXIAL-0.3EZ
RV1, RV2, RV4: 10k; ALPS_POT_KIT
RV3: 10k; POT_PANASONIC_DUAL_VERT_KIT
S1, S2, S3, S4, S6: SPDT; SWITCH-SPDT_KIT
S5: SWITCH-MOMENTARY-LEDEZ; TACTILE-PTH-LED-12MM-EZ
STANDOFF1, STANDOFF2, STANDOFF3, STANDOFF4: STAND-OFF

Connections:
BUTTON: D1.A, S5.2, S5.A
FILT-OUT: C11.2, IC3.7, JP13.1, RV3.A3, RV4.P$3
GND: BAT1.V-, C1.2, C2.2, C3.1, C4.2, C5.2, C12.1, C13.2, C16.2, IC1.7, IC2.4, IC2.6, IC2.7, IC2.8, IC2.10, IC3.4, IC4.4, J1.SLEEVE, JP15.1, JP17.1, R5.P$2, R13.P$1, R14.P$1, RV4.P$1, S1.3, S2.3, S3.3, S4.3
N: IC4.3, IC4.5, RV4.P$2
unnamed: D2.A, JP8.1
unnamed: C4.1, IC1.8, IC1.12, R4.P$1
unnamed: D1.C, D2.C, IC1.4, IC1.10, R5.P$1
unnamed: D3.A, S6.2
unnamed: JP6.1, R4.P$2, RV2.P$3
unnamed: R14.P$2, S5.C
unnamed: IC2.2, IC2.5
unnamed: IC2.9, IC2.12
unnamed: JP4.1, R3.P$2, RV1.P$3
unnamed: C10.2, S4.2
unnamed: J1.TSH, JP14.1
unnamed: C14.1, IC4.1, IC4.2
unnamed: C15.2, J1.RING
unnamed: C10.1, R10.P$2
unnamed: C9.1, R9.P$2
unnamed: C9.2, S3.2
unnamed: C6.2, JP9.1
unnamed: C6.1, R6.P$1
unnamed: C7.2, S1.2
unnamed: C8.2, S2.2
unnamed: C15.1, IC4.6, IC4.7
unnamed: IC3.2, R6.P$2, R7.P$1, R8.P$1, R9.P$1, R10.P$1, R11.P$2
unnamed: IC3.1, IC3.5, R11.P$1
unnamed: C8.1, R8.P$2
unnamed: C7.1, R7.P$2
unnamed: C14.2, J1.TIP
unnamed: C11.1, IC3.6, JP10.1, RV3.B1, RV3.B2
unnamed: C12.2, C13.1, JP11.1, JP12.1, RV3.A1, RV3.A2, RV3.B3
PITCH1: IC1.1, IC2.3, R1.P$1, S1.1
PITCH2: IC1.13, IC2.11, R2.P$1, S3.1
POT1: IC1.5, JP3.1, RV1.P$1, RV1.P$2
POT2: IC1.9, JP5.1, RV2.P$1, RV2.P$2
SUB1: IC2.1, S2.1
SUB2: IC2.13, S4.1
VBATT: BAT1.V+, S6.3
VCAP1: C3.2, IC1.2, IC1.6, JP7.1, R3.P$1
VCC: C5.1, C16.1, D3.C, IC1.14, IC2.14, IC3.8, IC4.8, JP16.1, R1.P$2, R2.P$2, R12.P$2, S5.4
VCC1: C2.1, IC1.11, JP2.1
VCC2: C1.1, IC1.3, JP1.1
VREF: IC3.3, R12.P$1, R13.P$2

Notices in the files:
parts and their libraries:
RELEASED UNDER THE CREATIVE COMMONS ATTRIBUTION SHARE-ALIKE 3.0 LICENSE
HTTP://CREATIVECOMMONS.ORG/LICENSES/BY-SA/3.0
RELEASED UNDER THE CREATIVE COMMONS ATTRIBUTION SHARE-ALIKE 4.0 LICENSE
HTTPS://CREATIVECOMMONS.ORG/LICENSES/BY-SA/4.0
